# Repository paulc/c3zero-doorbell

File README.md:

ESP32C3-Zero Doorbell Ring Detector (using Hall effect current sensor)

To plot raw samples (set SAMPLES & SAMPLE_RATE in examples/sample_timer.rs)

```
cargo run --release --example sample_timer | uv run --with matplotlib python plot.py
cargo run --release --example sample_continuous | uv run --with matplotlib python plot.py
```

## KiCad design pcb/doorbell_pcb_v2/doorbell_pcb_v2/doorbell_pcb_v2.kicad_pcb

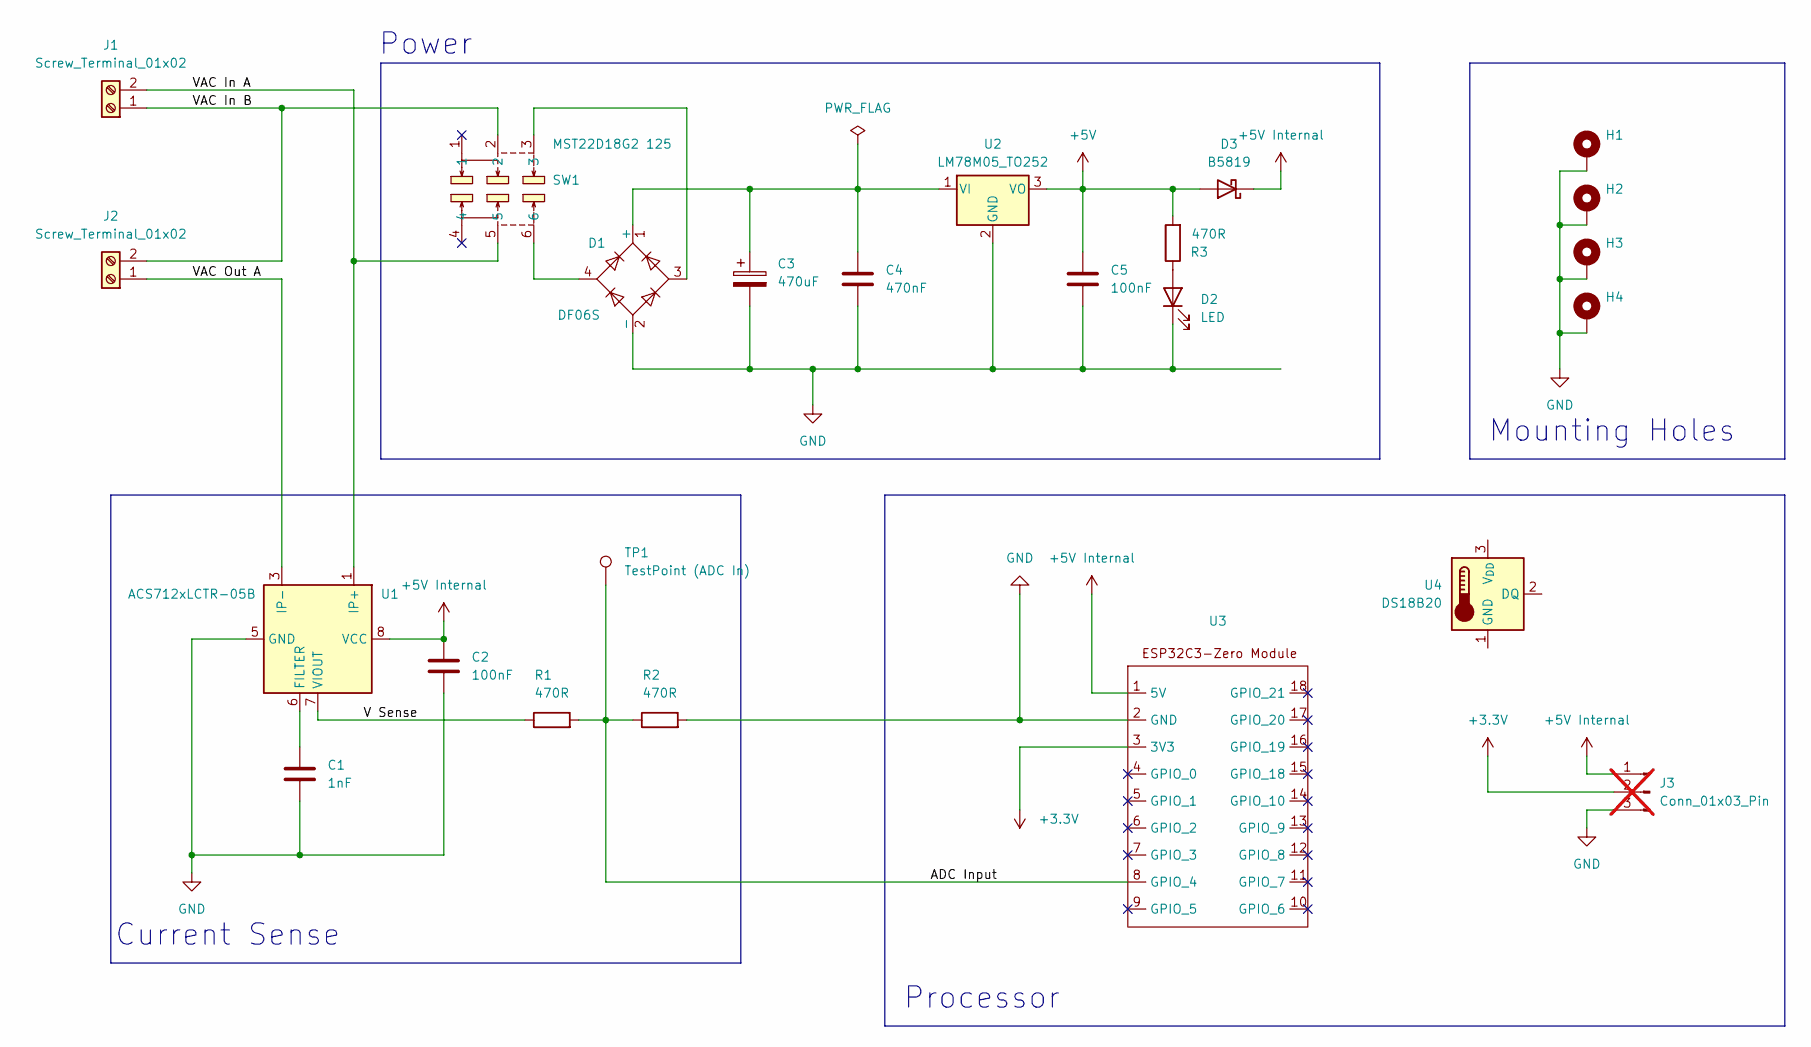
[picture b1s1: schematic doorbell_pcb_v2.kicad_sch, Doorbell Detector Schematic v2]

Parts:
C1: 1nF; C_0805_2012Metric_Pad1.18x1.45mm_HandSolder; LCSC C46653
C2, C5: 100nF; C_0805_2012Metric_Pad1.18x1.45mm_HandSolder; LCSC C49678
C3: 470uF; CP_Elec_10x10.5; LCSC C5162362
C4: 470nF; C_0805_2012Metric_Pad1.18x1.45mm_HandSolder; LCSC C13967
D1: DF06S; Diode_Bridge_OnSemi_SDIP-4L; LCSC C105154
D2: LED; LED_0805_2012Metric_Pad1.15x1.40mm_HandSolder; JLCPCB C84256
D3: B5819; D_SOD-123; LCSC C8598
H1, H2, H3, H4: MountingHole_Pad; MountingHole_2.2mm_M2_Pad
J1: Screw_Terminal_01x02; CONN-TH_P5.00_KF301-5.0-2P; LCSC C474881
J2: Screw_Terminal_01x02; CONN-TH_P5.00_KF301-5.0-2P; JLC C474881
J3: Conn_01x03_Pin; PinHeader_1x03_P2.54mm_Vertical; not fitted
R1, R2, R3: 470R; R_0805_2012Metric_Pad1.20x1.40mm_HandSolder; LCSC C17710
SW1: MST22D18G2 125; SW-SMD_MST22D18G2; LCSC Part C2906280
TP1: TestPoint (ADC In); TestPoint_THTPad_1.5x1.5mm_Drill0.7mm
U1: ACS712xLCTR-05B; SOIC-8_3.9x4.9mm_P1.27mm; LCSC C44471
U2: LM78M05_TO252; TO-252-2; LCSC C58069
U3: esp32c3-zero
U4: DS18B20; TO-92

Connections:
+3.3V: J3.2, U3.3 (3V3)
+5V: C5.1, D3.2 (A), R3.2, U2.3 (VO)
+5V Internal: C2.1, D3.1 (K), J3.1, U1.8 (VCC), U3.1 (5V)
/ADC Input: R1.2, R2.1, TP1.1, U3.8 (GPIO_4)
/V Sense: R1.1, U1.7 (VIOUT)
/VAC In A: J1.2, SW1.5, U1.1 (IP+), U1.2 (IP+)
/VAC In B: J1.1, J2.2, SW1.2
/VAC Out A: J2.1, U1.3 (IP-), U1.4 (IP-)
GND: C1.2, C2.2, C3.2, C4.2, C5.2, D1.2 (-), D2.1 (K), H1.1, H2.1, H3.1, H4.1, J3.3, R2.2, U1.5 (GND), U2.2 (GND), U3.2 (GND)
unnamed: C3.1, C4.1, D1.1 (+), U2.1 (VI)
unnamed: D1.3, SW1.3
unnamed: D1.4, SW1.6
unnamed: D2.2 (A), R3.1
unnamed: C1.1, U1.6 (FILTER)

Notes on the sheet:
Processor
Current Sense
Mounting Holes
Power

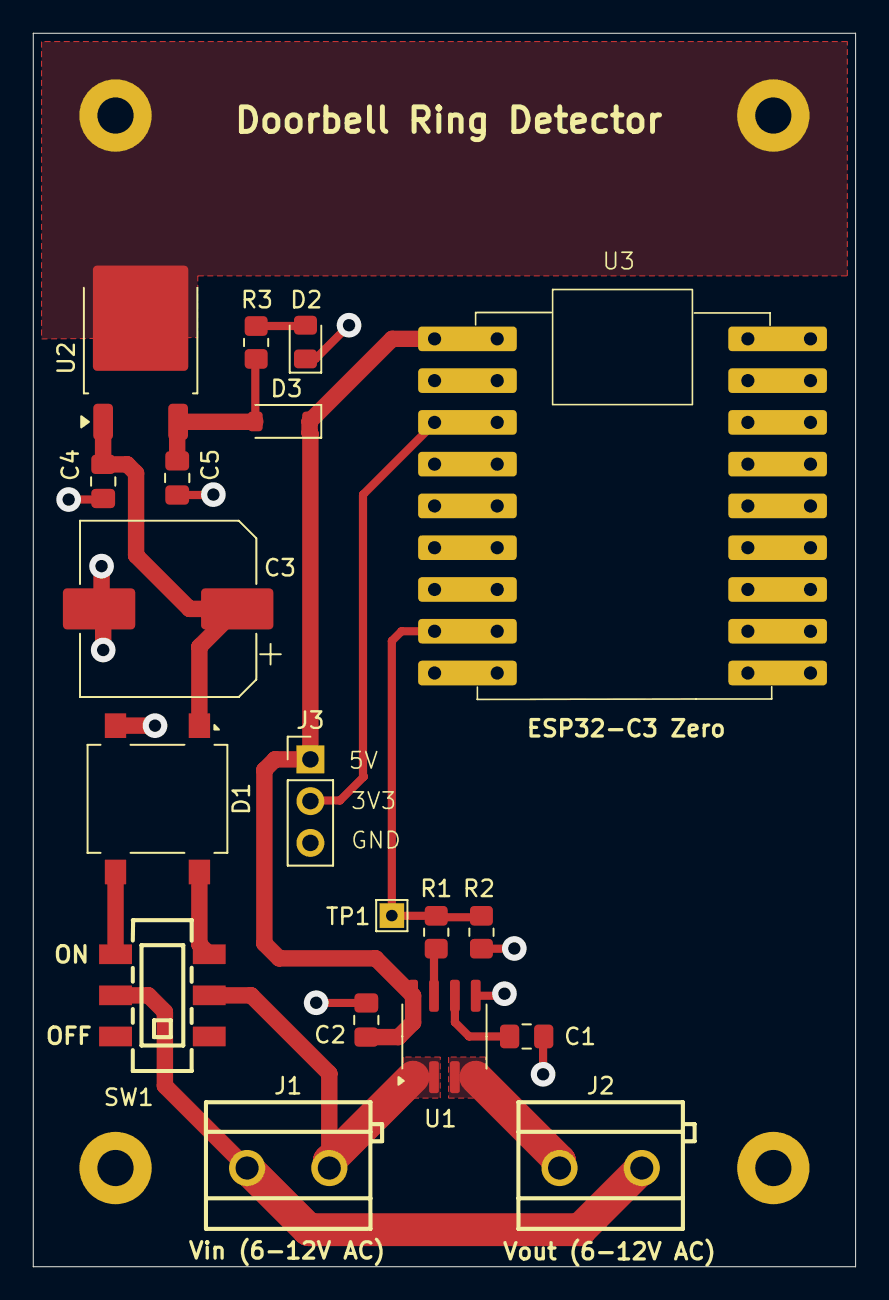
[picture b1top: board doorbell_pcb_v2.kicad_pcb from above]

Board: 2 copper layers, 50.0 x 75.0 mm, 23 parts (0 on the bottom side), 14 nets.

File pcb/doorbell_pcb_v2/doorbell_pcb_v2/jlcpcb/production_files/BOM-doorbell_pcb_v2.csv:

Comment,Designator,Footprint,LCSC,Quantity
DF06S,D1,Diode_Bridge_OnSemi_SDIP-4L,C105154,1
470nF,C4,C_0805_2012Metric_Pad1.18x1.45mm_HandSolder,C13967,1
470R,"R1,R2,R3",R_0805_2012Metric_Pad1.20x1.40mm_HandSolder,C17710,3
MST22D18G2 125,SW1,SW-SMD_MST22D18G2,C2906280,1
ACS712xLCTR-05B,U1,SOIC-8_3.9x4.9mm_P1.27mm,C44471,1
1nF,C1,C_0805_2012Metric_Pad1.18x1.45mm_HandSolder,C46653,1
100nF,"C2,C5",C_0805_2012Metric_Pad1.18x1.45mm_HandSolder,C49678,2
470uF,C3,CP_Elec_10x10.5,C5162362,1
LM78M05_TO252,U2,TO-252-2,C58069,1
LED,D2,LED_0805_2012Metric_Pad1.15x1.40mm_HandSolder,C84256,1
B5819,D3,D_SOD-123,C8598,1
Conn_01x03_Pin,,PinHeader_1x03_P2.54mm_Vertical,,0
TestPoint (ADC In),TP1,TestPoint_THTPad_1.5x1.5mm_Drill0.7mm,,1

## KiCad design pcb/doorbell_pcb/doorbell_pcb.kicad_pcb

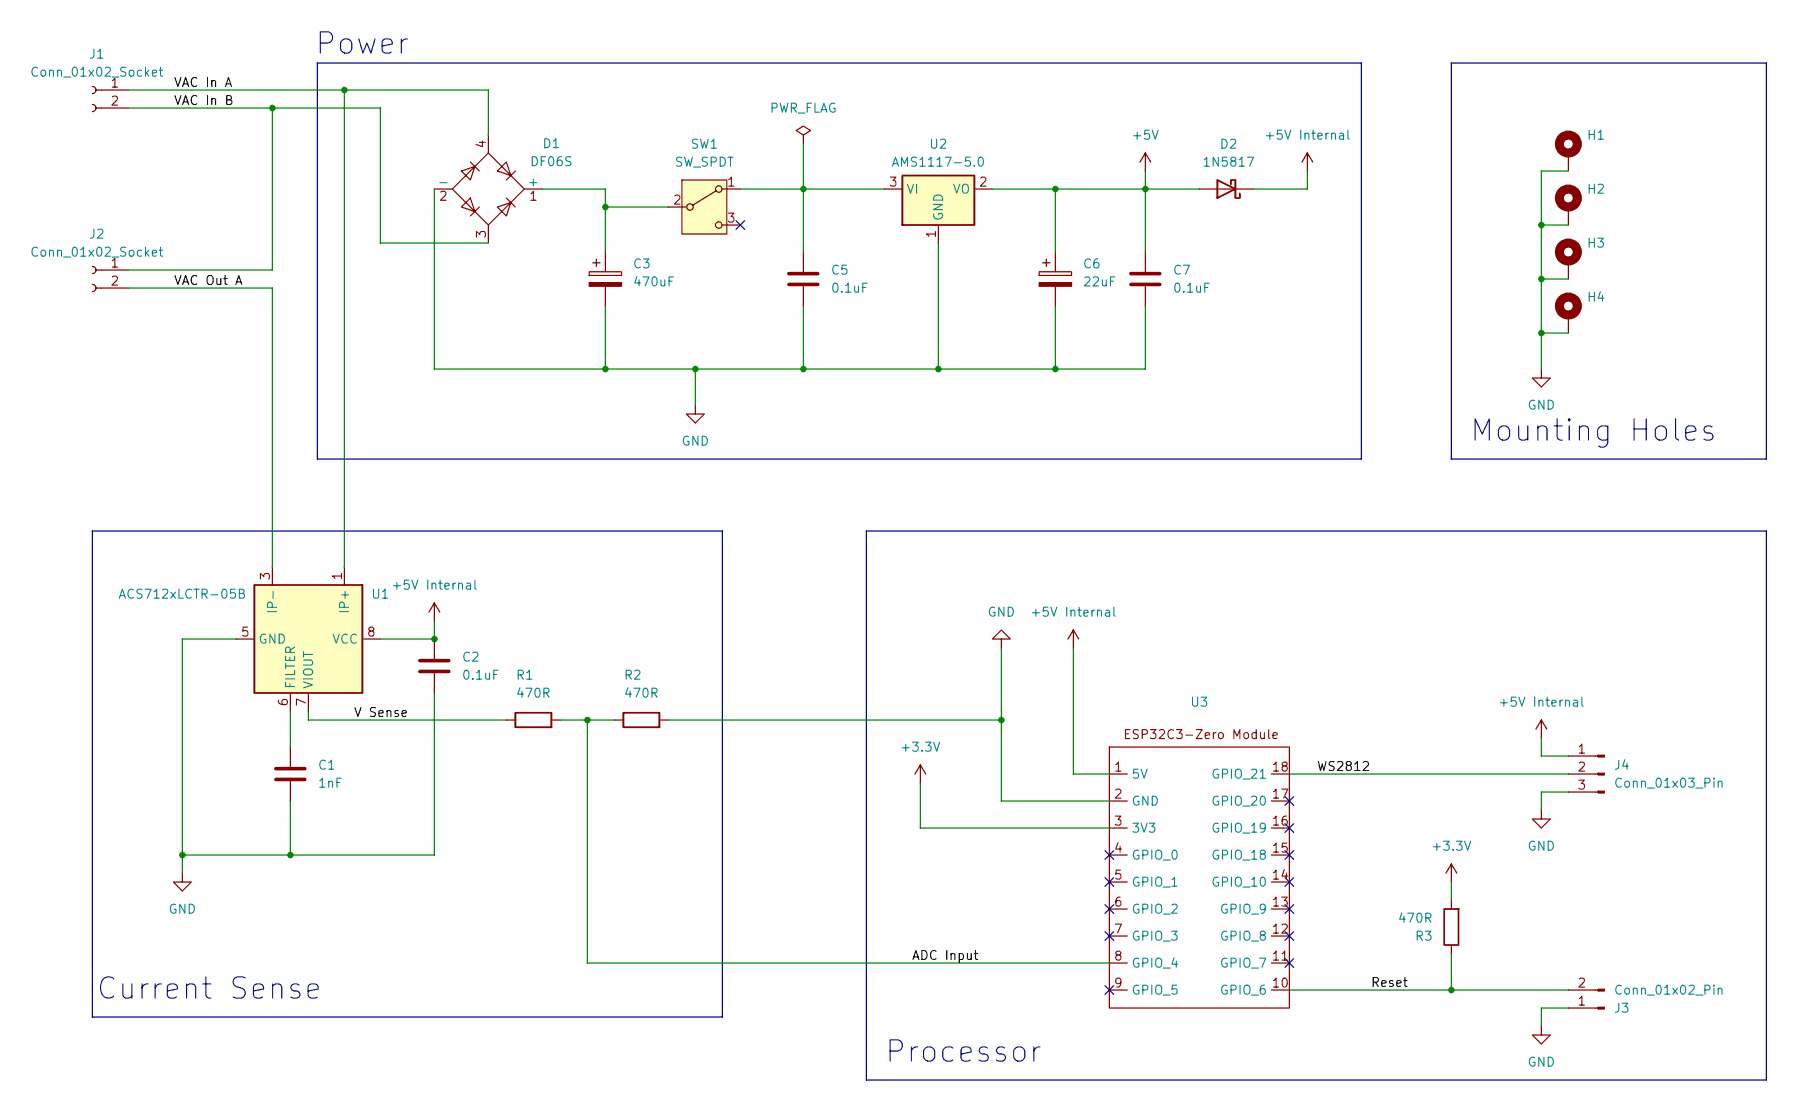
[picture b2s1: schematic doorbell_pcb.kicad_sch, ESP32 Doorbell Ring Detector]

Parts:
C1: 1nF; C_0805_2012Metric
C2, C5, C7: 0.1uF; C_0805_2012Metric
C3: 470uF; CP_Elec_10x10.5
C6: 22uF; CP_Elec_10x10.5
D1: DF06S; Diode_Bridge_OnSemi_SDIP-4L
D2: 1N5817; D_SOD-323
H1, H2, H3, H4: MountingHole_Pad; MountingHole_2.2mm_M2_Pad
J1, J2: Conn_01x02_Socket; TerminalBlock_Phoenix_MPT-0,5-2-2.54_1x02_P2.54mm_Horizontal
J3: Conn_01x02_Pin; JST_EH_B2B-EH-A_1x02_P2.50mm_Vertical
J4: Conn_01x03_Pin; JST_EH_B3B-EH-A_1x03_P2.50mm_Vertical
R1, R2, R3: 470R; R_0805_2012Metric
SW1: SW_SPDT; SW_SPDT_CK_JS102011SAQN
U1: ACS712xLCTR-05B; SOIC-8_3.9x4.9mm_P1.27mm
U2: AMS1117-5.0; SOT-223-3_TabPin2
U3: esp32c3-zero

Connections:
+3.3V: R3.2, U3.3 (3V3)
+5V: C6.1, C7.1, D2.2 (A), U2.2 (VO)
+5V Internal: C2.1, D2.1 (K), J4.1, U1.8 (VCC), U3.1 (5V)
/ADC Input: R1.2, R2.1, U3.8 (GPIO_4)
/Reset: J3.2, R3.1, U3.10 (GPIO_6)
/V Sense: R1.1, U1.7 (VIOUT)
/VAC In A: D1.4, J1.1, U1.1 (IP+), U1.2 (IP+)
/VAC In B: D1.3, J1.2, J2.1
/VAC Out A: J2.2, U1.3 (IP-), U1.4 (IP-)
/WS2812: J4.2, U3.18 (GPIO_21)
GND: C1.2, C2.2, C3.2, C5.2, C6.2, C7.2, D1.2 (-), H1.1, H2.1, H3.1, H4.1, J3.1, J4.3, R2.2, U1.5 (GND), U2.1 (GND), U3.2 (GND)
unnamed: C3.1, D1.1 (+), SW1.2 (B)
unnamed: C5.1, SW1.1 (A), U2.3 (VI)
unnamed: C1.1, U1.6 (FILTER)

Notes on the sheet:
Current Sense
Power
Mounting Holes
Processor

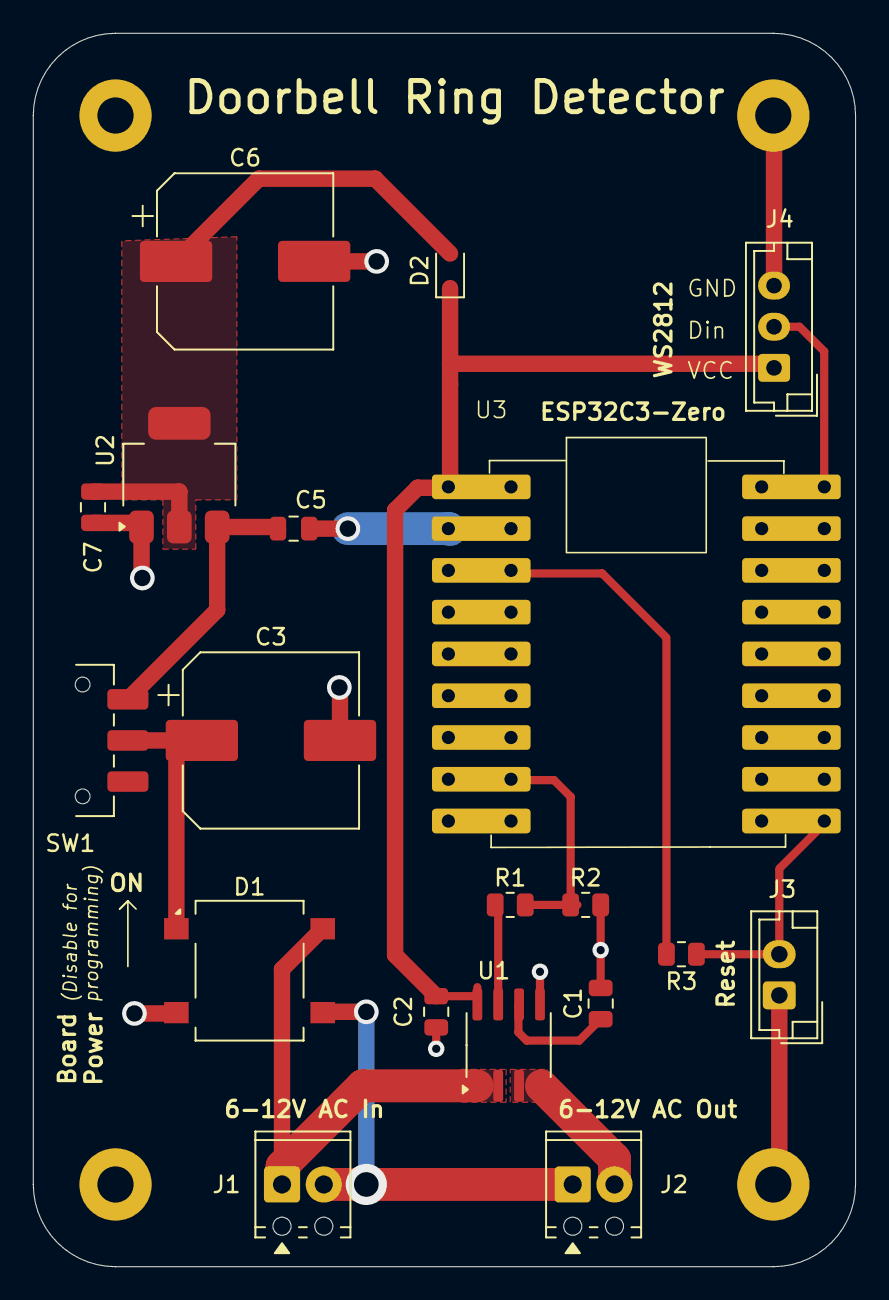
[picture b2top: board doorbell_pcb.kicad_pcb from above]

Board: 2 copper layers, 50.0 x 75.0 mm, 23 parts (0 on the bottom side), 14 nets.

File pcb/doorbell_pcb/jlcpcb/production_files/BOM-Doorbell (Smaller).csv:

Comment,Designator,Footprint,LCSC,Quantity
DF06S,D1,Diode_Bridge_OnSemi_SDIP-4L,C105154,1
470R,"R1,R2,R3",R_0805_2012Metric,C17710,3
SW_SPDT,SW1,SW_SPDT_CK_JS102011SAQN,C221660,1
22uF,C6,CP_Elec_10x10.5,C2910473,1
ACS712xLCTR-05B,U1,SOIC-8_3.9x4.9mm_P1.27mm,C44471,1
1nF,C1,C_0805_2012Metric,C46653,1
0.1uF,"C2,C5,C7",C_0805_2012Metric,C49678,3
AMS1117-5.0,U2,SOT-223-3_TabPin2,C6187,1
1N5817,D2,D_SOD-323,C727114,1
470uF,C3,CP_Elec_10x10.5,C96181,1

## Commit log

2025-05-19 Add README
2025-05-20 Tidy ip
2025-05-20 Tidy up
2025-05-24 Use timer/notification for ADC timing
2025-05-28 Continuous ADC driver
2025-05-28 Add wifi
2025-05-30 Fix ADC reset bug & add ring webhook
2025-05-31 Clippy fixes
2025-05-31 Clen up examples
2025-05-31 Clean up lib/mod structure
2025-06-01 NVS experiments
2025-06-02 Add generic NVStore & convert APStore
2025-06-02 NVStore updates
2025-06-03 Move ADC/Alert to tasks
2025-06-03 Status flash
2025-06-04 Check adc/alert tasks still running
2025-06-04 Add MQTT client
2025-06-06 MQTT alarm subscription example
2025-06-08 ws2812_quad
2025-06-19 Add NVS API endpoints / Add MQTT config NVS
2025-06-20 Add button_task
2025-06-21 Add button task
2025-06-21 Add button_closure
2025-06-21 Add PCB/Case
2025-06-24 Update template to use base.html, split style.css, and add navbar & flash components
2025-06-24 Fix navbar responsive width
2025-06-24 Update examples/mqtt web pages
2025-06-24 Interactive reset page
2025-06-25 Update reset_page to use AbortController
2025-06-26 Reset page
2025-06-26 URLEncode flash_msg cookie
2025-06-27 Restructured modules
2025-06-29 Refactoring
2025-06-30 Refactor lib/examples
2025-06-30 Include Auth Method
2025-07-01 Add SSE example
2025-07-02 Add MQTT handler
2025-07-03 MQTT updates
2025-07-03 Add MQTT error retry
2025-07-03 Try mqtt_client/connection - panics
2025-07-03 Switch to mqtt_chan handler
2025-07-03 mqtt_chan (clippy)
2025-07-04 mqtt
2025-07-05 TWDT investigation
2025-07-05 Looking for crash problem
2025-07-05 Misc fixes - add adc_stats http endpoint
2025-07-05 Add ring_stats / increase ring debounce
2025-07-06 Utils
2025-07-07 Delay updates to 30s
2025-07-07 Running version
2025-07-07 Development version - use dev MQTT server & dont send Pushover notifications
2025-07-10 Add TRIGGER const
2025-07-10 mqtt_connection
2025-07-11 MqttMessage channel / handle reconnect
2025-07-11 Modify doorbell::mqtt::MqttManager to use mqtt_connection code
2025-07-12 StaticMqttManager
2025-07-13 Add mqtt_task/web handlers
2025-07-13 Handle MQTT disconnects
2025-07-14 Initial OTA Support
2025-07-15 OTA updates
2025-07-15 Add OTA Valid
2025-07-16 OTA module
2025-07-16 Use partitions.csv in cargo run
2025-07-16 Add Default for Ota{}
2025-07-17 Add BuildInfo / HomePage
2025-07-18 Manage WiFi reconnection
2025-07-19 Update examples/mqtt
2025-07-20 Update WiFi state machine - handle disconnects more cleanly
2025-07-20 Doorbell example (initial)
2025-07-21 Refactor adc_task (probably need to revert)
2025-07-22 Refactor adc_task
2025-07-23 Add MQTT Configuration
2025-07-24 Add Pushover config
2025-07-26 Tidy up adc_task
2025-07-26 ADC waveform display
2025-07-27 Add ADC stats display
2025-07-27 Update rust-version
2025-07-28 Show OTA partition info on home page
2025-07-28 Configurable ADC threshold
2025-07-28 Updated PCB
2025-07-29 Minor fixes
2025-07-29 Update WiFi reconnection code
2025-07-29 Add mqtt_debug
2025-08-01 Add Pushover/MQTT test API endpoints
2025-08-02 Add static updated flag for mqtt/pushover settings
2025-08-03 Add debugging for MQTT hang
2025-08-05 Watchdog wrapper - avoid problem with subscription being droped if app_main exits
2025-08-06 Update watchdog code
2025-08-06 PCB updates
2025-08-07 Mqtt connect update
2025-09-04 pwm_task
2025-09-07 Remove unused alert lib crate
2025-09-07 Clean up examples / add TODO
2025-09-09 Add pwm_task module
2025-09-11 PWM set_frequency
2025-09-11 CLI OTA update util
